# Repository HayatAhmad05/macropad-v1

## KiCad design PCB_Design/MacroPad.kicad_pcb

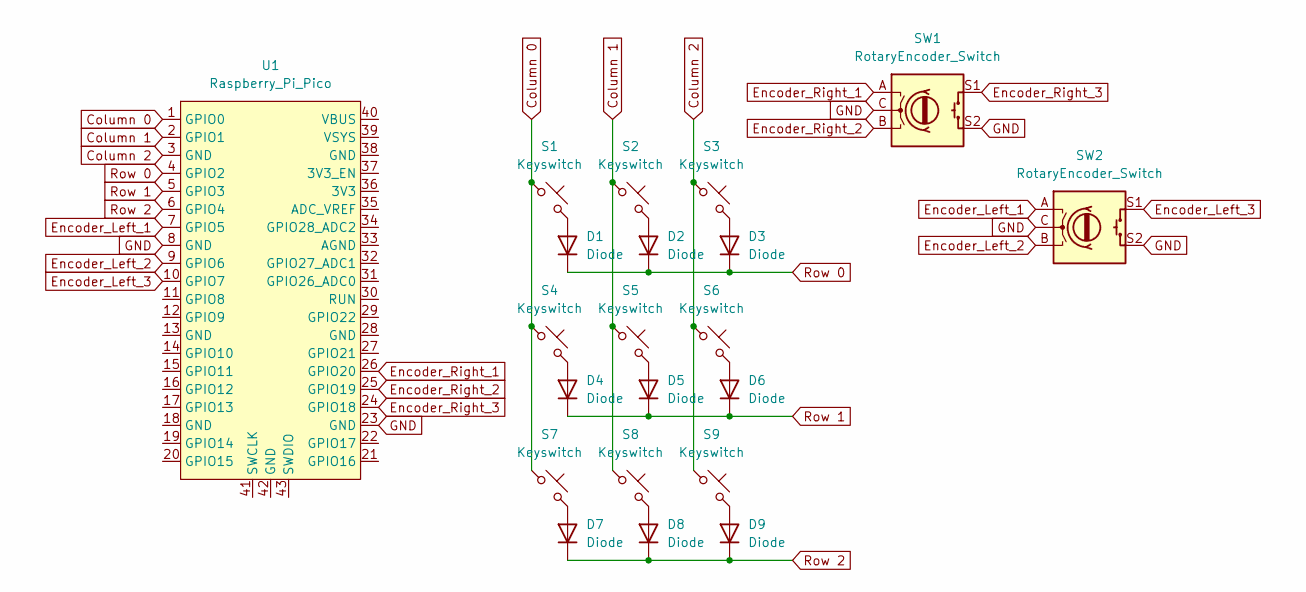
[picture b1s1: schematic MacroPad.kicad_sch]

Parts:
D1, D2, D3, D4, D5, D6, D7, D8, D9: Diode; Diode_DO-35
S1, S2, S3, S4, S5, S6, S7, S8, S9: Keyswitch; MX_PCB_1.00u
SW1, SW2: RotaryEncoder_Switch; RotaryEncoder_Bourns_Vertical_PEC12R-3x17F-Sxxxx
U1: Raspberry_Pi_Pico

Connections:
Column 0: S1.1, S4.1, S7.1, U1.1 (GPIO0)
Column 1: S2.1, S5.1, S8.1, U1.2 (GPIO1)
Column 2: S3.1, S6.1, S9.1, U1.3 (GND)
Encoder_Left_1: SW2.A, U1.7 (GPIO5)
Encoder_Left_2: SW2.B, U1.9 (GPIO6)
Encoder_Left_3: SW2.S1, U1.10 (GPIO7)
Encoder_Right_1: SW1.A, U1.26 (GPIO20)
Encoder_Right_2: SW1.B, U1.25 (GPIO19)
Encoder_Right_3: SW1.S1, U1.24 (GPIO18)
GND: SW1.C, SW1.S2, SW2.C, SW2.S2, U1.8 (GND), U1.23 (GND)
unnamed: D1.2 (A), S1.2
unnamed: D2.2 (A), S2.2
unnamed: D3.2 (A), S3.2
unnamed: D4.2 (A), S4.2
unnamed: D5.2 (A), S5.2
unnamed: D6.2 (A), S6.2
unnamed: D7.2 (A), S7.2
unnamed: D8.2 (A), S8.2
unnamed: D9.2 (A), S9.2
Row 0: D1.1 (K), D2.1 (K), D3.1 (K), U1.4 (GPIO2)
Row 1: D4.1 (K), D5.1 (K), D6.1 (K), U1.5 (GPIO3)
Row 2: D7.1 (K), D8.1 (K), D9.1 (K), U1.6 (GPIO4)

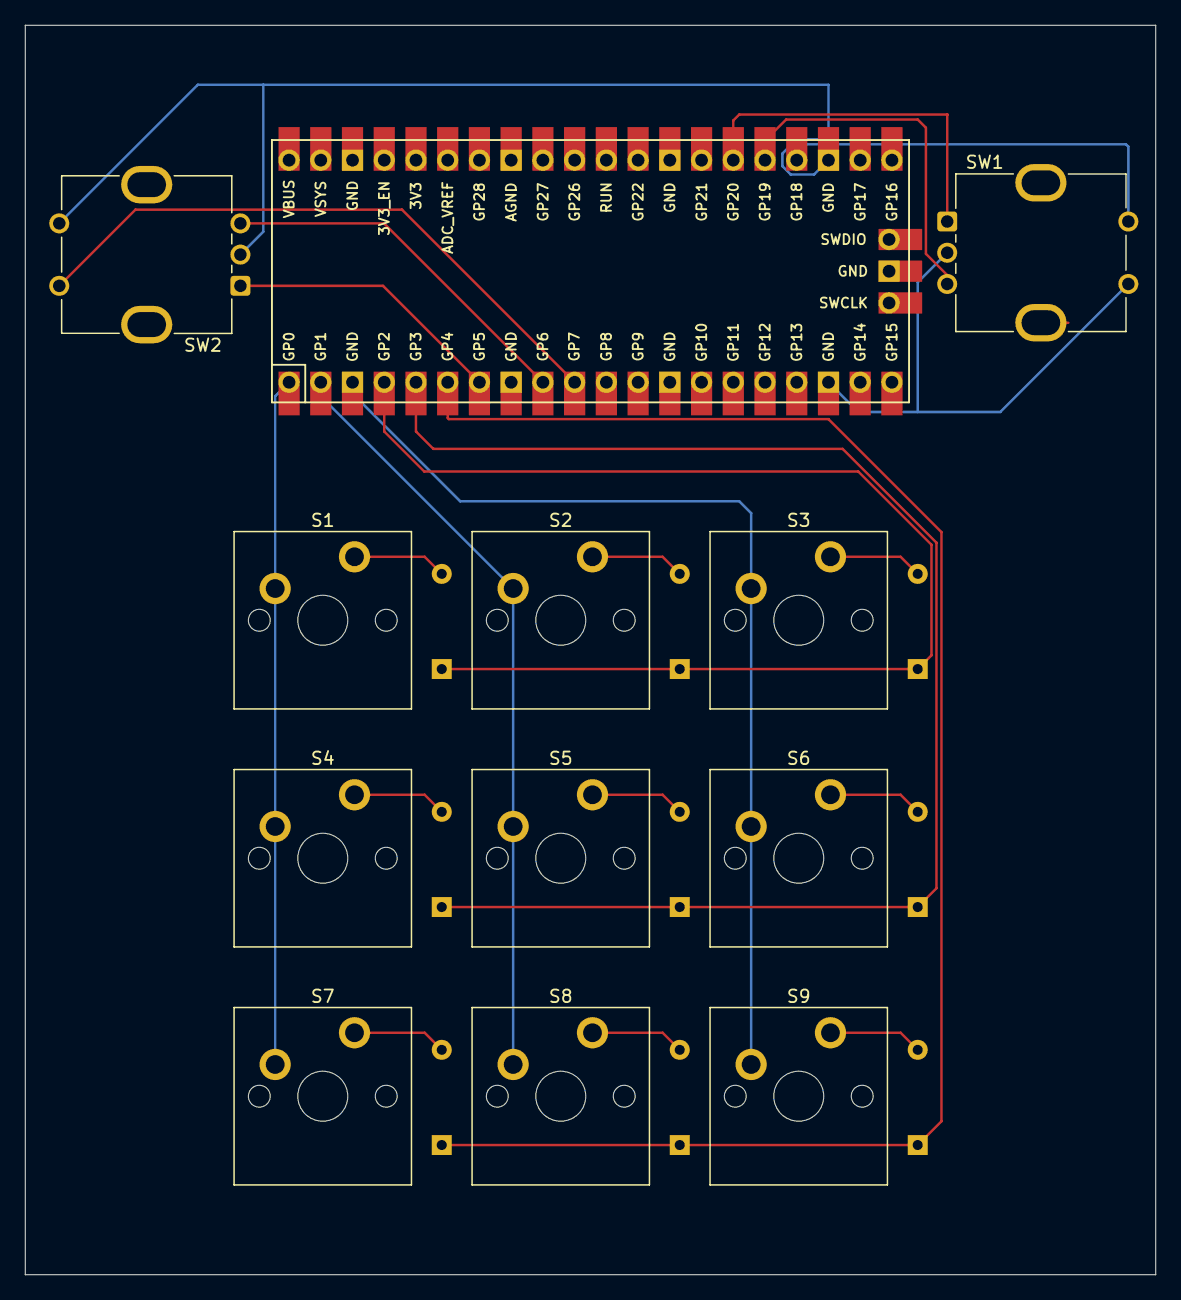
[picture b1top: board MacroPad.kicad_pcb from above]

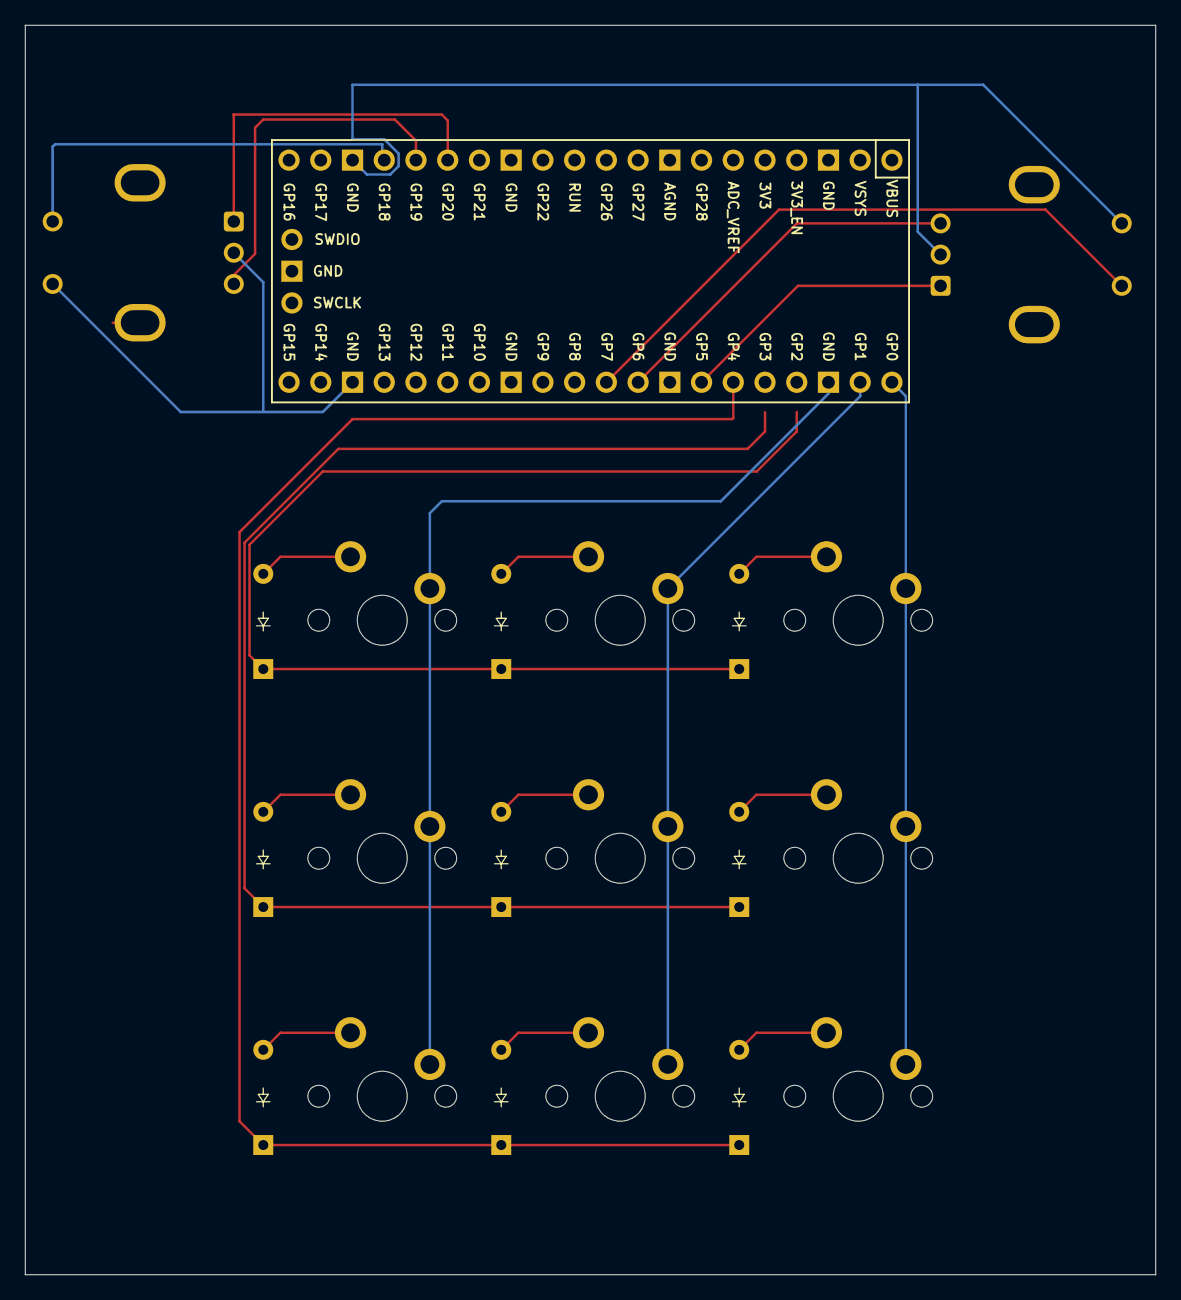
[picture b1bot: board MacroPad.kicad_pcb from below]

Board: 2 copper layers, 90.5 x 100.0 mm, 21 parts (9 on the bottom side), 22 nets.

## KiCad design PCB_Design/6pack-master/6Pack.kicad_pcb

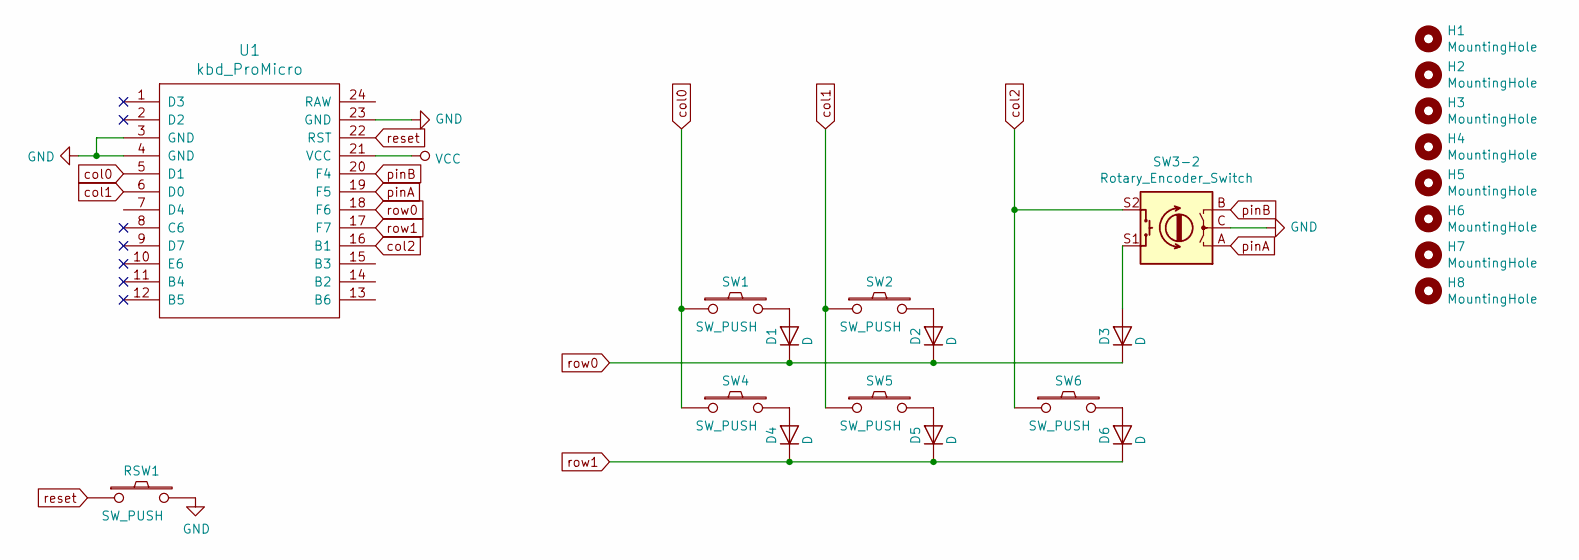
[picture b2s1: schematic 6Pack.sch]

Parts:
D1, D2, D3, D4, D5, D6: D; D_axial
H1, H2, H3, H4, H5, H6, H7, H8: MountingHole; MountingHole_2.2mm_M2
RSW1: SW_PUSH; SW_TACT_TH_HORIZ
SW1, SW2, SW4, SW5, SW6: SW_PUSH; MXOnly-1U
SW3-2: Rotary_Encoder_Switch; 1U-RotaryEncoder
U1: kbd_ProMicro; ArduinoProMicro

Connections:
GND: RSW1.2, SW3-2.C, U1.3 (GND), U1.4 (GND), U1.23 (GND)
unnamed: D1.2 (A), SW1.2
unnamed: D2.2 (A), SW2.2
unnamed: D3.2 (A), SW3-2.S1
unnamed: D4.2 (A), SW4.2
unnamed: D5.2 (A), SW5.2
unnamed: D6.2 (A), SW6.2
VCC: U1.21 (VCC)
col0: SW1.1, SW4.1, U1.5 (D1)
col1: SW2.1, SW5.1, U1.6 (D0)
col2: SW3-2.S2, SW6.1, U1.16 (B1)
pinA: SW3-2.A, U1.19 (F5)
pinB: SW3-2.B, U1.20 (F4)
reset: RSW1.1, U1.22 (RST)
row0: D1.1 (K), D2.1 (K), D3.1 (K), U1.18 (F6)
row1: D4.1 (K), D5.1 (K), D6.1 (K), U1.17 (F7)

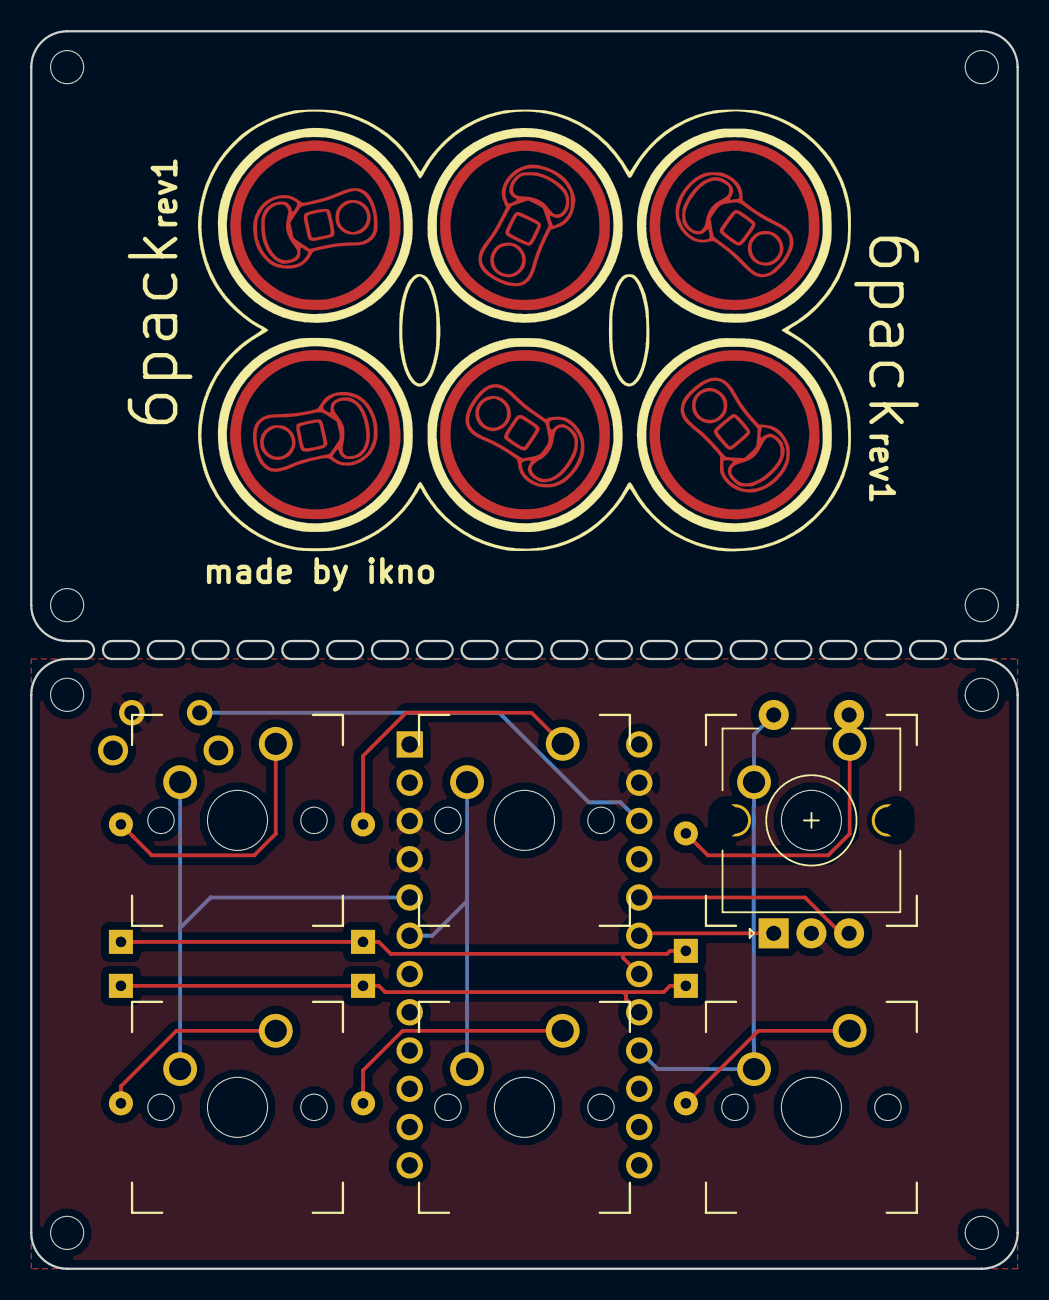
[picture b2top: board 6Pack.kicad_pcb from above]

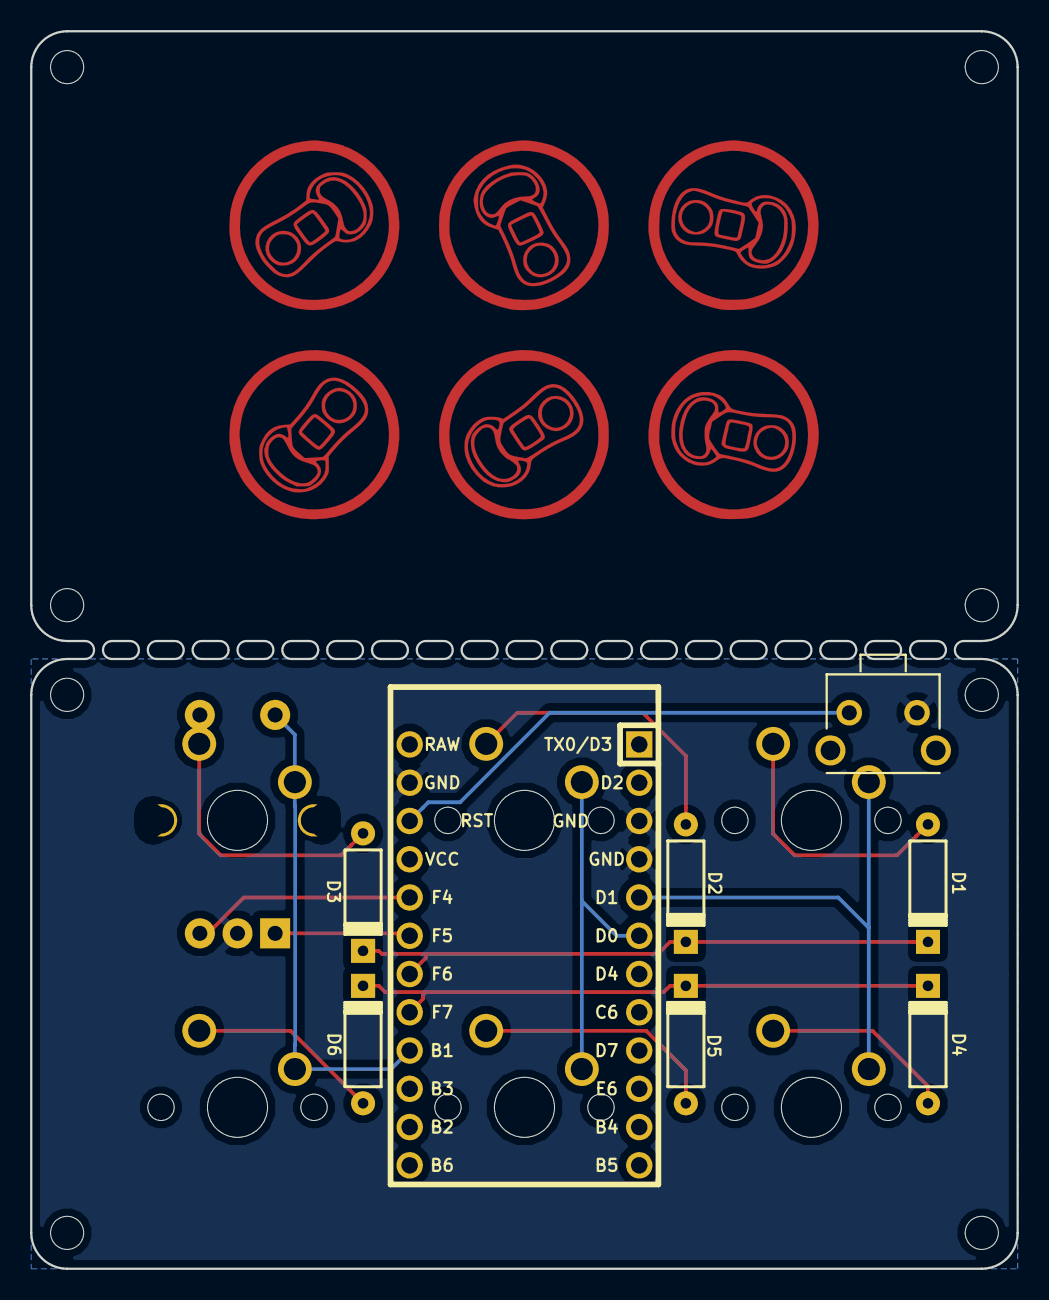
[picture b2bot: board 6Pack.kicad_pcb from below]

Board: 2 copper layers, 65.5 x 82.2 mm, 22 parts (7 on the bottom side), 15 nets.

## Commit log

2025-01-07 PCB Design Files
    Gerber files + Schematic Design + Footprints
2025-01-10 added main.py
2025-01-10 added custom macro script
